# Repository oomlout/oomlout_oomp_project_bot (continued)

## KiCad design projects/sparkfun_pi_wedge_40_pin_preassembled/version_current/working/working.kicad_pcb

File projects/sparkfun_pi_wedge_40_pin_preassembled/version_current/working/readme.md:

# Pi_Wedge_40-Pin_PreAssembled by sparkfun  
This is a harvested standardized copy of a project from github.  
The original project can be found at:  
https://github.com/sparkfun/Pi_Wedge_40-Pin_PreAssembled  
Please consult that link for additional, details, files, and license information.  
Note: It was auto harvested and if the original repo had more than one board file or anything out of the ordinary the files here are likely not representative.

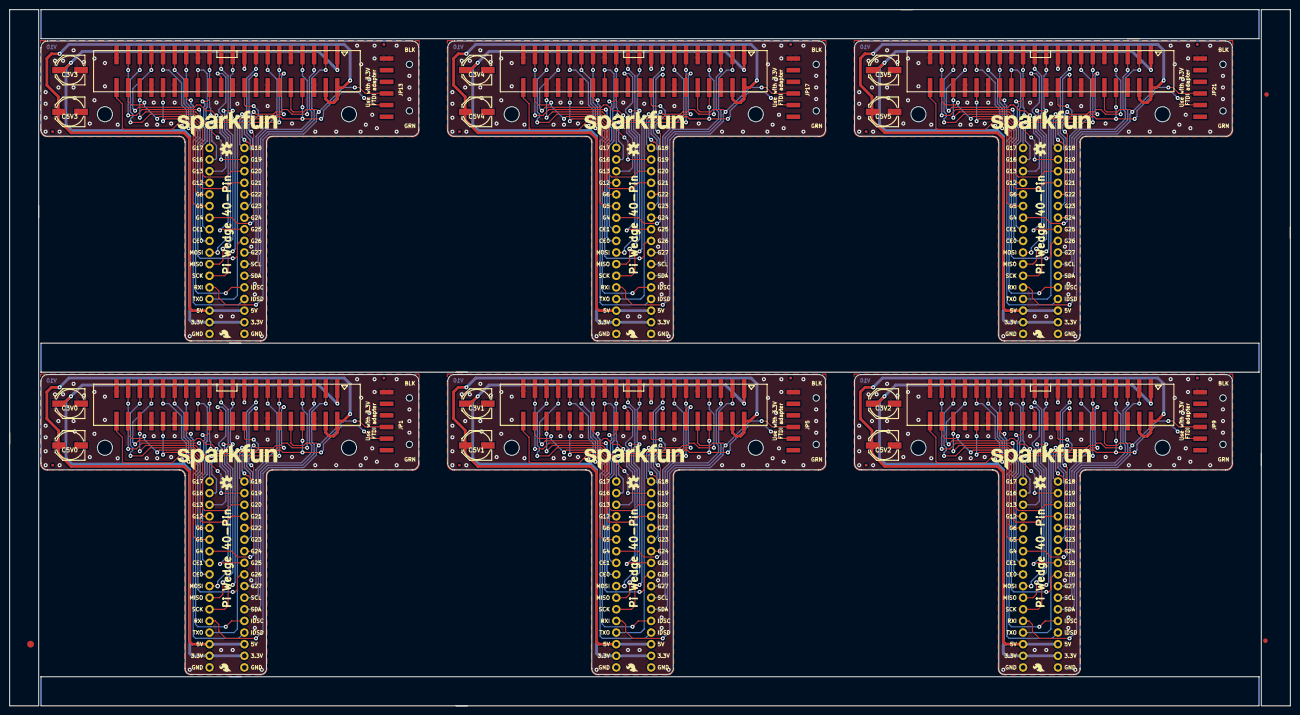
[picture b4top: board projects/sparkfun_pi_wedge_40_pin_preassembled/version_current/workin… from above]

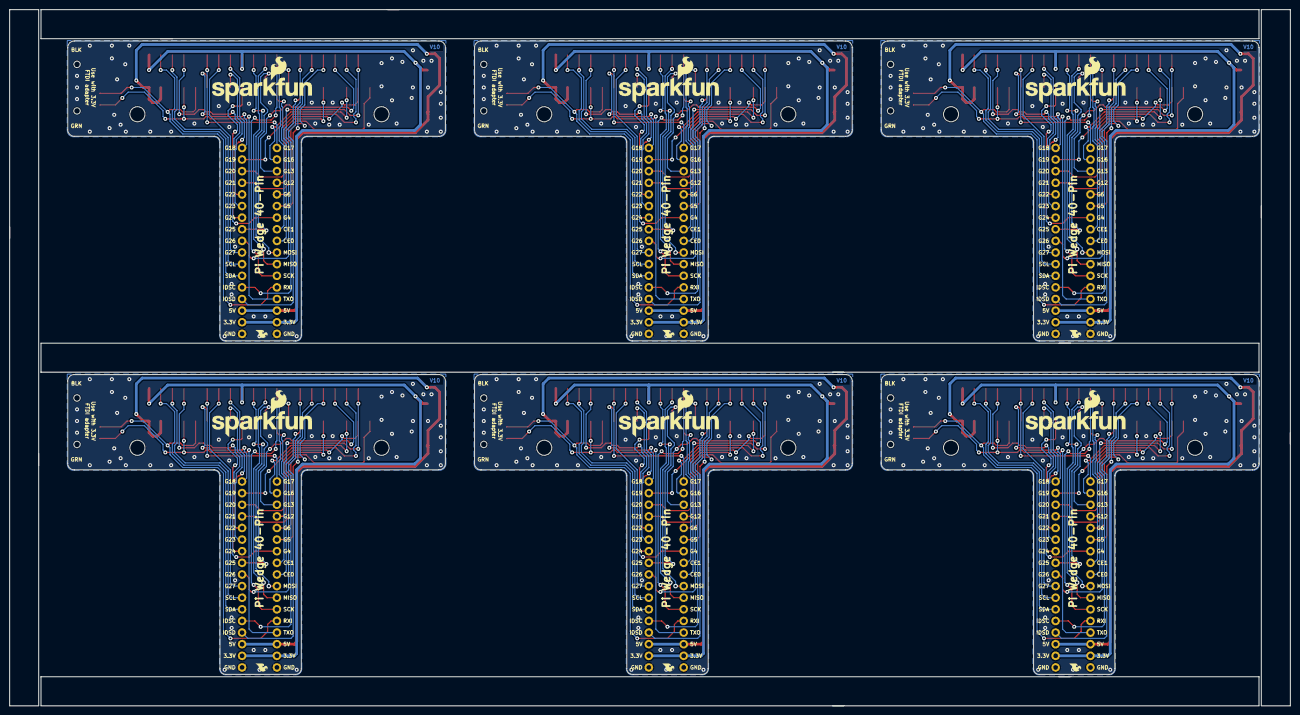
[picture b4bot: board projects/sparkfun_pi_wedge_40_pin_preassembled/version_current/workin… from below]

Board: 2 copper layers, 279.9 x 152.1 mm, 93 parts (24 on the bottom side), 186 nets.

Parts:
C3V0, C3V1, C3V2, C3V3, C3V4, C3V5, C5V0, C5V1, C5V2, C5V3, C5V4, C5V5: 10uf; PANASONIC_D
E$1: FIDUCIAL-1.5X3
E$5, E$6: FIDUCIAL-1X2
FID1, FID2, FID3, FID4, FID5, FID6, FID7, FID8, FID9, FID10, FID11, FID12: FIDUCIALUFIDUCIAL; MICRO-FIDUCIAL
JP1, JP5, JP9, JP13, JP17, JP21: FTDI Device; FTDI_DEVICE_RA_SMT
JP2, JP6, JP10, JP14, JP18, JP22: RASPBERRYPI-40-PIN-GPIO-SMT; 2X20-SHROUDED-SMT
JP3, JP4, JP7, JP8, JP11, JP12, JP15, JP16, JP19, JP20, JP23, JP24: 1x17; 1X17_NO_SILK_KIT
LOGO1, LOGO6, LOGO11, LOGO16, LOGO21, LOGO26: SFE_LOGO_NAME.2_INCH; SFE_LOGO_NAME_.2
LOGO2, LOGO7, LOGO12, LOGO17, LOGO22, LOGO27: SFE_LOGO_NAME_FLAME.2_INCH; SFE_LOGO_NAME_FLAME_.2
LOGO3, LOGO4, LOGO8, LOGO9, LOGO13, LOGO14, LOGO18, LOGO19, LOGO23, LOGO24, LOGO28, LOGO29: SFE_LOGO_FLAME.1_INCH; SFE_LOGO_FLAME_.1
LOGO5, LOGO10, LOGO15, LOGO20, LOGO25, LOGO30: OSHW-LOGOS; OSHW-LOGO-S
STANDOFF1, STANDOFF2, STANDOFF3, STANDOFF4, STANDOFF5, STANDOFF6, STANDOFF7, STANDOFF8, STANDOFF9, STANDOFF10, STANDOFF11, STANDOFF12: STAND-OFF

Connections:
3.3V: C3V0.+, JP2.1, JP2.17, JP3.2, JP4.2
3.3V1: C3V1.+, JP6.1, JP6.17, JP7.2, JP8.2
3.3V2: C3V2.+, JP10.1, JP10.17, JP11.2, JP12.2
3.3V3: C3V3.+, JP14.1, JP14.17, JP15.2, JP16.2
3.3V4: C3V4.+, JP18.1, JP18.17, JP19.2, JP20.2
3.3V5: C3V5.+, JP22.1, JP22.17, JP23.2, JP24.2
5V: C5V0.+, JP2.2, JP2.4, JP3.3, JP4.3
5V1: C5V1.+, JP6.2, JP6.4, JP7.3, JP8.3
5V2: C5V2.+, JP10.2, JP10.4, JP11.3, JP12.3
5V3: C5V3.+, JP14.2, JP14.4, JP15.3, JP16.3
5V4: C5V4.+, JP18.2, JP18.4, JP19.3, JP20.3
5V5: C5V5.+, JP22.2, JP22.4, JP23.3, JP24.3
CE0: JP2.24, JP3.9
CE1: JP2.26, JP3.10
CE2: JP6.24, JP7.9
CE3: JP6.26, JP7.10
CE4: JP10.24, JP11.9
CE5: JP10.26, JP11.10
CE6: JP14.24, JP15.9
CE7: JP14.26, JP15.10
CE8: JP18.24, JP19.9
CE9: JP18.26, JP19.10
CE10: JP22.24, JP23.9
CE11: JP22.26, JP23.10
GND: C3V0.-, C5V0.-, JP1.6, JP2.6, JP2.9, JP2.14, JP2.20, JP2.25, JP2.30, JP2.34, JP2.39, JP3.1, JP4.1
GND1: C3V1.-, C5V1.-, JP5.6, JP6.6, JP6.9, JP6.14, JP6.20, JP6.25, JP6.30, JP6.34, JP6.39, JP7.1, JP8.1
GND2: C3V2.-, C5V2.-, JP9.6, JP10.6, JP10.9, JP10.14, JP10.20, JP10.25, JP10.30, JP10.34, JP10.39, JP11.1, JP12.1
GND3: C3V3.-, C5V3.-, JP13.6, JP14.6, JP14.9, JP14.14, JP14.20, JP14.25, JP14.30, JP14.34, JP14.39, JP15.1, JP16.1
GND4: C3V4.-, C5V4.-, JP17.6, JP18.6, JP18.9, JP18.14, JP18.20, JP18.25, JP18.30, JP18.34, JP18.39, JP19.1, JP20.1
GND5: C3V5.-, C5V5.-, JP21.6, JP22.6, JP22.9, JP22.14, JP22.20, JP22.25, JP22.30, JP22.34, JP22.39, JP23.1, JP24.1
GP1: JP6.7, JP7.11
GP2: JP6.13, JP8.8
GP3: JP6.22, JP8.10
GP4: JP2.7, JP3.11
GP5: JP2.29, JP3.12
GP6: JP2.31, JP3.13
GP7: JP6.18, JP8.11
GP8: JP6.16, JP8.12
GP9: JP6.15, JP8.13
GP10: JP6.12, JP8.17
GP11: JP6.11, JP7.17
GP12: JP2.32, JP3.14
GP13: JP2.33, JP3.15
GP14: JP6.29, JP7.12
GP15: JP6.31, JP7.13
GP16: JP2.36, JP3.16
GP17: JP2.11, JP3.17
GP18: JP2.12, JP4.17
GP19: JP2.35, JP4.16
GP20: JP2.38, JP4.15
GP21: JP2.40, JP4.14
GP22: JP2.15, JP4.13
GP23: JP2.16, JP4.12
GP24: JP2.18, JP4.11
GP25: JP2.22, JP4.10
GP26: JP2.37, JP4.9
GP27: JP2.13, JP4.8
GP28: JP6.32, JP7.14
GP29: JP6.33, JP7.15
GP30: JP6.36, JP7.16
GP31: JP6.35, JP8.16
GP32: JP6.38, JP8.15
GP33: JP6.40, JP8.14
GP34: JP6.37, JP8.9
GP35: JP10.7, JP11.11
GP36: JP10.13, JP12.8
GP37: JP10.22, JP12.10
GP38: JP10.18, JP12.11
GP39: JP10.16, JP12.12
GP40: JP10.15, JP12.13
GP41: JP10.12, JP12.17
GP42: JP10.11, JP11.17
GP43: JP10.29, JP11.12
GP44: JP10.31, JP11.13
GP45: JP10.32, JP11.14
GP46: JP10.33, JP11.15
GP47: JP10.36, JP11.16
GP48: JP10.35, JP12.16
GP49: JP10.38, JP12.15
GP50: JP10.40, JP12.14
GP51: JP10.37, JP12.9
GP52: JP14.7, JP15.11
GP53: JP14.13, JP16.8
GP54: JP14.22, JP16.10
GP55: JP14.18, JP16.11
GP56: JP14.16, JP16.12
GP57: JP14.15, JP16.13
GP58: JP14.12, JP16.17
GP59: JP14.11, JP15.17
GP60: JP14.29, JP15.12
GP61: JP14.31, JP15.13
GP62: JP14.32, JP15.14
GP63: JP14.33, JP15.15
GP64: JP14.36, JP15.16
GP65: JP14.35, JP16.16
GP66: JP14.38, JP16.15
GP67: JP14.40, JP16.14
GP68: JP14.37, JP16.9
GP69: JP18.7, JP19.11
GP70: JP18.13, JP20.8
GP71: JP18.22, JP20.10
GP72: JP18.18, JP20.11
GP73: JP18.16, JP20.12
GP74: JP18.15, JP20.13
GP75: JP18.12, JP20.17
GP76: JP18.11, JP19.17
GP77: JP18.29, JP19.12
GP78: JP18.31, JP19.13
GP79: JP18.32, JP19.14
GP80: JP18.33, JP19.15
GP81: JP18.36, JP19.16
GP82: JP18.35, JP20.16
GP83: JP18.38, JP20.15
GP84: JP18.40, JP20.14
GP85: JP18.37, JP20.9
GP86: JP22.7, JP23.11
GP87: JP22.13, JP24.8
GP88: JP22.22, JP24.10
GP89: JP22.18, JP24.11
GP90: JP22.16, JP24.12
GP91: JP22.15, JP24.13
GP92: JP22.12, JP24.17
GP93: JP22.11, JP23.17
GP94: JP22.29, JP23.12
GP95: JP22.31, JP23.13
GP96: JP22.32, JP23.14
GP97: JP22.33, JP23.15
GP98: JP22.36, JP23.16
GP99: JP22.35, JP24.16
GP100: JP22.38, JP24.15
GP101: JP22.40, JP24.14
GP102: JP22.37, JP24.9
ID_SC: JP2.28, JP4.5
ID_SC1: JP6.28, JP8.5
ID_SC2: JP10.28, JP12.5
ID_SC3: JP14.28, JP16.5
ID_SC4: JP18.28, JP20.5
ID_SC5: JP22.28, JP24.5
ID_SD: JP2.27, JP4.4
ID_SD1: JP6.27, JP8.4
ID_SD2: JP10.27, JP12.4
ID_SD3: JP14.27, JP16.4
ID_SD4: JP18.27, JP20.4
ID_SD5: JP22.27, JP24.4
MISO: JP2.21, JP3.7
MISO1: JP6.21, JP7.7
MISO2: JP10.21, JP11.7
MISO3: JP14.21, JP15.7
MISO4: JP18.21, JP19.7
MISO5: JP22.21, JP23.7
MOSI: JP2.19, JP3.8
MOSI1: JP6.19, JP7.8
MOSI2: JP10.19, JP11.8
MOSI3: JP14.19, JP15.8
MOSI4: JP18.19, JP19.8
MOSI5: JP22.19, JP23.8
RXI: JP1.3, JP2.10, JP3.5
RXI1: JP5.3, JP6.10, JP7.5
RXI2: JP9.3, JP10.10, JP11.5
RXI3: JP13.3, JP14.10, JP15.5
RXI4: JP17.3, JP18.10, JP19.5
RXI5: JP21.3, JP22.10, JP23.5
SCL: JP2.5, JP4.7
SCL1: JP6.5, JP8.7
SCL2: JP10.5, JP12.7
SCL3: JP14.5, JP16.7
SCL4: JP18.5, JP20.7
SCL5: JP22.5, JP24.7
SCLK: JP2.23, JP3.6
SCLK1: JP6.23, JP7.6
SCLK2: JP10.23, JP11.6
SCLK3: JP14.23, JP15.6
SCLK4: JP18.23, JP19.6
SCLK5: JP22.23, JP23.6
SDA: JP2.3, JP4.6
SDA1: JP6.3, JP8.6
SDA2: JP10.3, JP12.6
SDA3: JP14.3, JP16.6
SDA4: JP18.3, JP20.6
SDA5: JP22.3, JP24.6
TXO: JP1.2, JP2.8, JP3.4
TXO1: JP5.2, JP6.8, JP7.4
TXO2: JP9.2, JP10.8, JP11.4
TXO3: JP13.2, JP14.8, JP15.4
TXO4: JP17.2, JP18.8, JP19.4
TXO5: JP21.2, JP22.8, JP23.4

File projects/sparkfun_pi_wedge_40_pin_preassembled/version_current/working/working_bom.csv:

Row,Description,Part,References,Value,Footprint,Quantity Per PCB,Status,Datasheet
1,,47UF-50V-20%(ELECT),C3V0 C5V0,47uf,PANASONIC_D,2, ,
2,,FRAME-LETTER,FRAME2,FRAME-LETTER,CREATIVE_COMMONS,1, ,
3,,M17KIT,JP3 JP4,1x17,1X17_NO_SILK_KIT,2, ,
4,,FTDI_DEVICERA_SMT,JP1,FTDI_DEVICERA_SMT,FTDI_DEVICE_RA_SMT,1, ,
5,,RASPBERRYPI-40-PIN-GPIO-SMT,JP2,RASPBERRYPI-40-PIN-GPIO-SMT,2X20-SHROUDED-SMT,1, ,
6,,OSHW-LOGOS,LOGO5,OSHW-LOGOS,OSHW-LOGO-S,1, ,
7,,SFE_LOGO_FLAME.1_INCH,LOGO3 LOGO4,SFE_LOGO_FLAME.1_INCH,SFE_LOGO_FLAME_.1,2, ,
8,,SFE_LOGO_NAME.2_INCH,LOGO1,SFE_LOGO_NAME.2_INCH,SFE_LOGO_NAME_.2,1, ,
9,,SFE_LOGO_NAME_FLAME.2_INCH,LOGO2,SFE_LOGO_NAME_FLAME.2_INCH,SFE_LOGO_NAME_FLAME_.2,1, ,
10,,STAND-OFF,STANDOFF1 STANDOFF2,STAND-OFF,STAND-OFF,2, ,
11,,BREADBOARD_PATTERN,U$2,BREADBOARD_PATTERN,BREADBOARD_SPACING,1, ,





Project info:
Schematic:,working
Variant:,default
Revision:,
Date:,2023-08-06_12-56-12
KiCad Version:,7.0.6-7.0.6~ubuntu22.04.1
Statistics:
Component Groups:,11
Component Count:,15 (0 SMD/ 0 THT)
Fitted Components:,15 (0 SMD/ 0 THT)
Number of PCBs:,1
Total Components:,15

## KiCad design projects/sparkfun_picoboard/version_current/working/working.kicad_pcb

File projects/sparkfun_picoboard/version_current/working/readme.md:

# OOMP Project  
## PicoBoard  by sparkfun  
  
oomp key: oomp_projects_flat_sparkfun_picoboard  
(snippet of original readme)  
  
Picoboard  
=========  
  
[   
*PicoBoard (WIG-10311)*](https://www.sparkfun.com/products/10311)  
  
The PicoBoard allows you to interface hardware sensors with the Scratch programming language.  

Repository Contents  
-------------------  
* **/hardware** - All Eagle design files (.brd, .sch, .STL)  
* **/firmware** - PicoBoard source code for an ATmega328.  
  
License Information  
-------------------  
The contents released under [Creative Commons Share-alike 3.0](http://creativecommons.org/licenses/by-sa/3.0/).    
  full source readme at [readme_src.md](readme_src.md)  
  
source repo at: [https://github.com/sparkfun/PicoBoard](https://github.com/sparkfun/PicoBoard)  
## Board  

## Schematic  

[schematic pdf](working_schematic.pdf)  
## Images

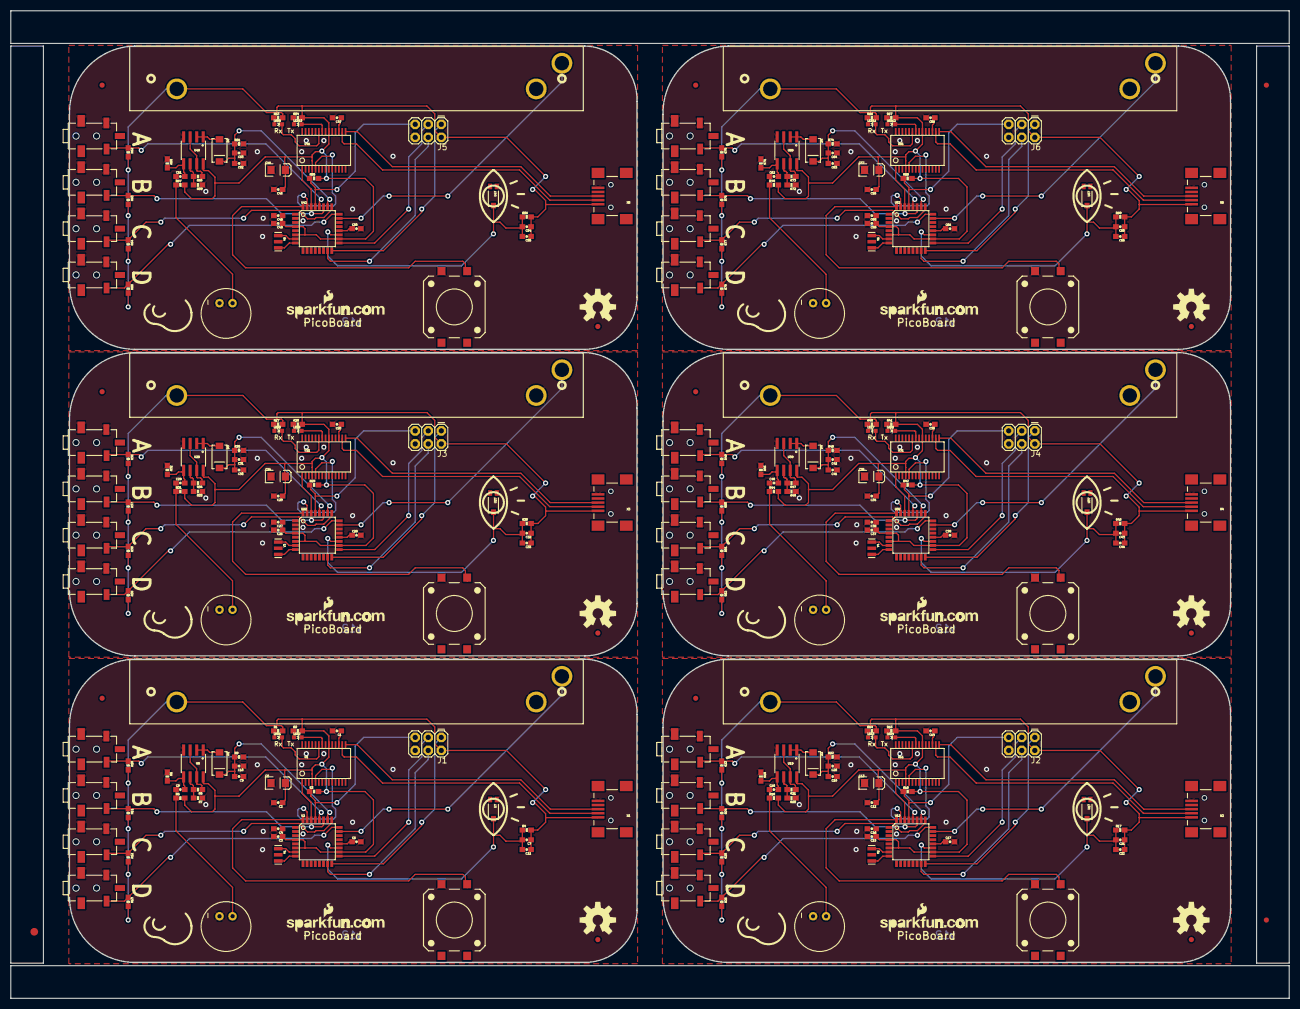
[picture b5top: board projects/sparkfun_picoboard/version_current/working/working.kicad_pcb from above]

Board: 2 copper layers, 248.9 x 192.3 mm, 273 parts (0 on the bottom side), 186 nets.

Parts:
C1, C2, C3, C4, C6, C8, C9, C10, C11, C12, C14, C15, C16, C17, C18, C19, C20, C22, C23, C25, C26, C27, C28, C29, C30, C31, C33, C34, C36, C37, C38, C39, C40, C41, C42, C44, C45, C47, C48, C49, C50, C51, C52, C53, C55, C56, C58, C59, C60, C61, C62, C63, C64, C66: 0.1uF; 0603-CAP
C5, C13, C24, C35, C46, C57: 10uF; EIA3216
C7, C21, C32, C43, C54, C65: 0.22uF; 0603-CAP
D1, D2, D3, D4, D5, D6: MBRA140; SMA-DIODE
E$1: FIDUCIAL-1.5X3
E$2, E$4: FIDUCIAL-1X2
FID1, FID2, FID3, FID4, FID5, FID6, FID7, FID8, FID9, FID10, FID11, FID12: FIDUCIAL1X2; FIDUCIAL-1X2
J1, J2, J3, J4, J5, J6: AVR Prog.; 2X3
JP1, JP2, JP3, JP4, JP5, JP6: LOGO-SFENEW; SFE-NEW-WEBLOGO
LED1, LED3, LED5, LED7, LED9, LED11: Red; LED-0603
LED2, LED4, LED6, LED8, LED10, LED12: Green; LED-0603
LOGO1, LOGO2, LOGO3, LOGO4, LOGO5, LOGO6: OSHW-LOGOL; OSHW-LOGO-L
R1, R2, R14, R15, R27, R28, R40, R41, R53, R54, R66, R67: 1K; 0603-RES
R3, R5, R6, R10, R11, R12, R13, R16, R18, R19, R23, R24, R25, R26, R29, R31, R32, R36, R37, R38, R39, R42, R44, R45, R49, R50, R51, R52, R55, R57, R58, R62, R63, R64, R65, R68, R70, R71, R75, R76, R77, R78: 10k; 0603-RES
R4, R8, R9, R17, R21, R22, R30, R34, R35, R43, R47, R48, R56, R60, R61, R69, R73, R74: 100k; 0603-RES
R7, R20, R33, R46, R59, R72: 2.2k; 0603-RES
S1, S2, S3, S4, S5, S6: 12mm Button; TACTILE-SMD-12MM
U1, U11, U21, U31, U41, U51: FT232RLSSOP; SSOP28DB
U2, U12, U22, U32, U42, U52: ATMEGA328; TQFP32-08
U3, U4, U5, U6, U13, U14, U15, U16, U23, U24, U25, U26, U33, U34, U35, U36, U43, U44, U45, U46, U53, U54, U55, U56: 2.5mm; STEREOJACK2.5MM
U7, U17, U27, U37, U47, U57: TEMT6000; TEMT6000-SEN
U8, U19, U29, U39, U49, U59: LMV358; SO08
U9, U18, U28, U38, U48, U58: MIC9.7MM; MIC-9.7MM
U10, U20, U30, U40, U50, U60: SLIDER
X1, X2, X3, X4, X5, X6: USBSMD; USB-MINIB
Y1, Y2, Y3, Y4, Y5, Y6: 16MHz; RESONATOR-SMD

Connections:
3.3V: C1.1, U1.17
3.3V1: C14.1, U11.17
3.3V2: C25.1, U21.17
3.3V3: C36.1, U31.17
3.3V4: C47.1, U41.17
3.3V5: C58.1, U51.17
5V: C2.1, C3.1, C4.1, C5.A, C7.1, C11.1, J1.2, R1.2, R2.2, R3.2, R4.2, R5.2, R10.2, R11.2, R12.2, R13.2, U1.4, U1.20, U2.4, U2.6, U2.18, U8.8, U10.3, X1.VBUS
5V1: C12.1, C13.A, C15.1, C16.1, C21.1, C22.1, J2.2, R14.2, R15.2, R16.2, R17.2, R18.2, R23.2, R24.2, R25.2, R26.2, U11.4, U11.20, U12.4, U12.6, U12.18, U19.8, U20.3, X2.VBUS
5V2: C23.1, C24.A, C26.1, C27.1, C32.1, C33.1, J3.2, R27.2, R28.2, R29.2, R30.2, R31.2, R36.2, R37.2, R38.2, R39.2, U21.4, U21.20, U22.4, U22.6, U22.18, U29.8, U30.3, X3.VBUS
5V3: C34.1, C35.A, C37.1, C38.1, C43.1, C44.1, J4.2, R40.2, R41.2, R42.2, R43.2, R44.2, R49.2, R50.2, R51.2, R52.2, U31.4, U31.20, U32.4, U32.6, U32.18, U39.8, U40.3, X4.VBUS
5V4: C45.1, C46.A, C48.1, C49.1, C54.1, C55.1, J5.2, R53.2, R54.2, R55.2, R56.2, R57.2, R62.2, R63.2, R64.2, R65.2, U41.4, U41.20, U42.4, U42.6, U42.18, U49.8, U50.3, X5.VBUS
5V5: C56.1, C57.A, C59.1, C60.1, C65.1, C66.1, J6.2, R66.2, R67.2, R68.2, R69.2, R70.2, R75.2, R76.2, R77.2, R78.2, U51.4, U51.20, U52.4, U52.6, U52.18, U59.8, U60.3, X6.VBUS
GND: C1.2, C2.2, C3.2, C4.2, C5.C, C6.2, C9.1, C10.1, J1.6, R6.1, R7.1, R9.2, S2.3, U1.7, U1.18, U1.21, U1.25, U1.26, U2.3, U2.5, U2.21, U3.1, U3.5, U4.1, U4.5, U5.1, U5.5, U6.1, U6.5, U7.EMITTER, U8.4, U9.2, U10.1, X1.GND, Y1.2
GND1: C12.2, C13.C, C14.2, C15.2, C16.2, C17.2, C19.1, C20.1, J2.6, R19.1, R20.1, R22.2, S1.3, U11.7, U11.18, U11.21, U11.25, U11.26, U12.3, U12.5, U12.21, U13.1, U13.5, U14.1, U14.5, U15.1, U15.5, U16.1, U16.5, U17.EMITTER, U18.2, U19.4, U20.1, X2.GND, Y2.2
GND2: C23.2, C24.C, C25.2, C26.2, C27.2, C28.2, C30.1, C31.1, J3.6, R32.1, R33.1, R35.2, S3.3, U21.7, U21.18, U21.21, U21.25, U21.26, U22.3, U22.5, U22.21, U23.1, U23.5, U24.1, U24.5, U25.1, U25.5, U26.1, U26.5, U27.EMITTER, U28.2, U29.4, U30.1, X3.GND, Y3.2
GND3: C34.2, C35.C, C36.2, C37.2, C38.2, C39.2, C41.1, C42.1, J4.6, R45.1, R46.1, R48.2, S4.3, U31.7, U31.18, U31.21, U31.25, U31.26, U32.3, U32.5, U32.21, U33.1, U33.5, U34.1, U34.5, U35.1, U35.5, U36.1, U36.5, U37.EMITTER, U38.2, U39.4, U40.1, X4.GND, Y4.2
GND4: C45.2, C46.C, C47.2, C48.2, C49.2, C50.2, C52.1, C53.1, J5.6, R58.1, R59.1, R61.2, S5.3, U41.7, U41.18, U41.21, U41.25, U41.26, U42.3, U42.5, U42.21, U43.1, U43.5, U44.1, U44.5, U45.1, U45.5, U46.1, U46.5, U47.EMITTER, U48.2, U49.4, U50.1, X5.GND, Y5.2
GND5: C56.2, C57.C, C58.2, C59.2, C60.2, C61.2, C63.1, C64.1, J6.6, R71.1, R72.1, R74.2, S6.3, U51.7, U51.18, U51.21, U51.25, U51.26, U52.3, U52.5, U52.21, U53.1, U53.5, U54.1, U54.5, U55.1, U55.5, U56.1, U56.5, U57.EMITTER, U58.2, U59.4, U60.1, X6.GND, Y6.2
LIGHT: C7.2, C11.2, R4.1, U2.19, U7.COLLECTOR
LIGHT1: C21.2, C22.2, R17.1, U12.19, U17.COLLECTOR
LIGHT2: C32.2, C33.2, R30.1, U22.19, U27.COLLECTOR
LIGHT3: C43.2, C44.2, R43.1, U32.19, U37.COLLECTOR
LIGHT4: C54.2, C55.2, R56.1, U42.19, U47.COLLECTOR
LIGHT5: C65.2, C66.2, R69.1, U52.19, U57.COLLECTOR
MISO: J1.1, U2.16
MISO1: J2.1, U12.16
MISO2: J3.1, U22.16
MISO3: J4.1, U32.16
MISO4: J5.1, U42.16
MISO5: J6.1, U52.16
MOSI: J1.4, U2.15
MOSI1: J2.4, U12.15
MOSI2: J3.4, U22.15
MOSI3: J4.4, U32.15
MOSI4: J5.4, U42.15
MOSI5: J6.4, U52.15
unnamed: LED1.A, R1.1
unnamed: LED2.A, R2.1
unnamed: R7.2, R8.2, U8.6
unnamed: LED3.A, R14.1
unnamed: U2.7, Y1.1
unnamed: U2.8, Y1.3
unnamed: C6.1, U2.20
unnamed: S2.1, U2.32
unnamed: C8.1, R5.1, U9.1
unnamed: U2.23, U10.2A
unnamed: C8.2, R6.2, U8.5
unnamed: LED4.A, R15.1
unnamed: D1.A, U8.1, U8.2
unnamed: U12.7, Y2.1
unnamed: U12.8, Y2.3
unnamed: R8.1, U8.3, U8.7
unnamed: C17.1, U12.20
unnamed: S1.1, U12.32
unnamed: C18.1, R18.1, U18.1
unnamed: C18.2, R19.2, U19.5
unnamed: R20.2, R21.2, U19.6
unnamed: D2.A, U19.1, U19.2
unnamed: R21.1, U19.3, U19.7
unnamed: U12.23, U20.2A
unnamed: LED5.A, R27.1
unnamed: LED6.A, R28.1
unnamed: U22.7, Y3.1
unnamed: U22.8, Y3.3
unnamed: C28.1, U22.20
unnamed: S3.1, U22.32
unnamed: C29.1, R31.1, U28.1
unnamed: C29.2, R32.2, U29.5
unnamed: R33.2, R34.2, U29.6
unnamed: D3.A, U29.1, U29.2
unnamed: R34.1, U29.3, U29.7
unnamed: U22.23, U30.2A
unnamed: LED7.A, R40.1
unnamed: LED8.A, R41.1
unnamed: U32.7, Y4.1
unnamed: U32.8, Y4.3
unnamed: C39.1, U32.20
unnamed: S4.1, U32.32
unnamed: C40.1, R44.1, U38.1
unnamed: C40.2, R45.2, U39.5
unnamed: R46.2, R47.2, U39.6
unnamed: D4.A, U39.1, U39.2
unnamed: R47.1, U39.3, U39.7
unnamed: U32.23, U40.2A
unnamed: LED9.A, R53.1
unnamed: LED10.A, R54.1
unnamed: U42.7, Y5.1
unnamed: U42.8, Y5.3
unnamed: C50.1, U42.20
unnamed: S5.1, U42.32
unnamed: C51.1, R57.1, U48.1
unnamed: C51.2, R58.2, U49.5
unnamed: R59.2, R60.2, U49.6
unnamed: D5.A, U49.1, U49.2
unnamed: R60.1, U49.3, U49.7
unnamed: U42.23, U50.2A
unnamed: LED11.A, R66.1
unnamed: LED12.A, R67.1
unnamed: U52.7, Y6.1
unnamed: U52.8, Y6.3
unnamed: C61.1, U52.20
unnamed: S6.1, U52.32
unnamed: C62.1, R70.1, U58.1
unnamed: C62.2, R71.2, U59.5
unnamed: R72.2, R73.2, U59.6
unnamed: D6.A, U59.1, U59.2
unnamed: R73.1, U59.3, U59.7
unnamed: U52.23, U60.2A
RA: R10.1, U2.28, U3.4
RA1: R23.1, U12.28, U13.4
RA2: R36.1, U22.28, U23.4
RA3: R49.1, U32.28, U33.4
RA4: R62.1, U42.28, U43.4
RA5: R75.1, U52.28, U53.4
RB: R11.1, U2.27, U4.4
RB1: R24.1, U12.27, U14.4
RB2: R37.1, U22.27, U24.4
RB3: R50.1, U32.27, U34.4
RB4: R63.1, U42.27, U44.4
RB5: R76.1, U52.27, U54.4
RC: R12.1, U2.25, U5.4
RC1: R25.1, U12.25, U15.4
RC2: R38.1, U22.25, U25.4
RC3: R51.1, U32.25, U35.4
RC4: R64.1, U42.25, U45.4
RC5: R77.1, U52.25, U55.4
RD: R13.1, U2.24, U6.4
RD1: R26.1, U12.24, U16.4
RD2: R39.1, U22.24, U26.4
RD3: R52.1, U32.24, U36.4
RD4: R65.1, U42.24, U46.4
RD5: R78.1, U52.24, U56.4
RES: J1.5, R3.1, U2.29
RES1: J2.5, R16.1, U12.29
RES2: J3.5, R29.1, U22.29
RES3: J4.5, R42.1, U32.29
RES4: J5.5, R55.1, U42.29
RES5: J6.5, R68.1, U52.29
RXI: U1.1, U2.30
RXI1: U11.1, U12.30
RXI2: U21.1, U22.30
RXI3: U31.1, U32.30
RXI4: U41.1, U42.30
RXI5: U51.1, U52.30
RXLED: LED2.C, U1.22
RXLED1: LED4.C, U11.22
RXLED2: LED6.C, U21.22
RXLED3: LED8.C, U31.22
RXLED4: LED10.C, U41.22
RXLED5: LED12.C, U51.22
SCK: J1.3, U2.17
SCK1: J2.3, U12.17
SCK2: J3.3, U22.17
SCK3: J4.3, U32.17
SCK4: J5.3, U42.17
SCK5: J6.3, U52.17
SOUND: C9.2, C10.2, D1.C, R9.1, U2.26
SOUND1: C19.2, C20.2, D2.C, R22.1, U12.26
SOUND2: C30.2, C31.2, D3.C, R35.1, U22.26
SOUND3: C41.2, C42.2, D4.C, R48.1, U32.26
SOUND4: C52.2, C53.2, D5.C, R61.1, U42.26
SOUND5: C63.2, C64.2, D6.C, R74.1, U52.26
TXLED: LED1.C, U1.23
TXLED1: LED3.C, U11.23
TXLED2: LED5.C, U21.23
TXLED3: LED7.C, U31.23
TXLED4: LED9.C, U41.23
TXLED5: LED11.C, U51.23
TXO: U1.5, U2.31
TXO1: U11.5, U12.31
TXO2: U21.5, U22.31
TXO3: U31.5, U32.31
TXO4: U41.5, U42.31
TXO5: U51.5, U52.31
USB_D+: U1.15, X1.D+
USB_D+1: U11.15, X2.D+
USB_D+2: U21.15, X3.D+
USB_D+3: U31.15, X4.D+
USB_D+4: U41.15, X5.D+
USB_D+5: U51.15, X6.D+
USB_D-: U1.16, X1.D-
USB_D-1: U11.16, X2.D-
USB_D-2: U21.16, X3.D-
USB_D-3: U31.16, X4.D-
USB_D-4: U41.16, X5.D-
USB_D-5: U51.16, X6.D-

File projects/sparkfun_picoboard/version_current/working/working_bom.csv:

Row,Description,Part,References,Value,Footprint,Quantity Per PCB,Status,Datasheet
1,,CAP0603-CAP,C1 C2 C3 C4 C6 C8 C9 C10 C11,0.1uF,0603-CAP,9, ,
2,,CAP0603-CAP,C7,0.22uF,0603-CAP,1, ,
3,,CAP_POL1206,C5,10uF,EIA3216,1, ,
4,,DIODESMA,D1,MBRA140,SMA-DIODE,1, ,
5,,FRAME-LETTER,FRAME1,FRAME-LETTER,CREATIVE_COMMONS,1, ,
6,,AVR_SPI_PRG_6PTH,J1,AVR_SPI_PRG_6PTH,2X3,1, ,
7,,LOGO-SFENEW,JP1,LOGO-SFENEW,SFE-NEW-WEBLOGO,1, ,
8,,LED0603,LED2,Green,LED-0603,1, ,
9,,LED0603,LED1,Red,LED-0603,1, ,
10,,OSHW-LOGOL,LOGO1,OSHW-LOGOL,OSHW-LOGO-L,1, ,
11,,RESISTOR0603-RES,R1 R2,1K,0603-RES,2, ,
12,,RESISTOR0603-RES,R7,2.2k,0603-RES,1, ,
13,,RESISTOR0603-RES,R3 R5 R6 R10 R11 R12 R13,10k,0603-RES,7, ,
14,,RESISTOR0603-RES,R4 R8 R9,100k,0603-RES,3, ,
15,,SWITCH-MOMENTARY-2SMD-12MM,S2,SWITCH-MOMENTARY-2SMD-12MM,TACTILE-SMD-12MM,1, ,
16,,AUDIO-JACK1{colon}1,U3 U4 U5 U6,2.5mm,STEREOJACK2.5MM,4, ,
17,,ATMEGA168,U2,ATMEGA168,TQFP32-08,1, ,
18,,FT232RLSSOP,U1,FT232RLSSOP,SSOP28DB,1, ,
19,,LMV358,U8,LMV358,SO08,1, ,
20,,MIC9.7MM,U9,MIC9.7MM,MIC-9.7MM,1, ,
21,,SLIDER60MM,U10,SLIDER60MM,SLIDER,1, ,
22,,TEMT6000,U7,TEMT6000,TEMT6000-SEN,1, ,
23,,USBSMD,X1,USBSMD,USB-MINIB,1, ,
24,,RESONATORSMD,Y1,RESONATORSMD,RESONATOR-SMD,1, ,





Project info:
Schematic:,working
Variant:,default
Revision:,
Date:,2023-08-06_12-56-12
KiCad Version:,7.0.6-7.0.6~ubuntu22.04.1
Statistics:
Component Groups:,24
Component Count:,44 (0 SMD/ 0 THT)
Fitted Components:,44 (0 SMD/ 0 THT)
Number of PCBs:,1
Total Components:,44

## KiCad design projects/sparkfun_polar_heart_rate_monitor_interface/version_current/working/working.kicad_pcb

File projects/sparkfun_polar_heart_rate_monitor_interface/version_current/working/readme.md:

# OOMP Project  
## Polar_Heart_Rate_Monitor_Interface  by sparkfun  
  
oomp key: oomp_projects_flat_sparkfun_polar_heart_rate_monitor_interface  
(snippet of original readme)  
  
SparkFun Polar Heart Rate Monitor Interface  
========================================  

[*SparkFun Polar Heart Rate Monitor Interface (SEN-08661)*](https://www.sparkfun.com/products/8661)  
  
The Heart Rate Monitor Interface (HRMI) is an intelligent peripheral device that converts the ECG signal from the Polar Heart Rate Monitor (HRM)   
into easy-to-use heart rate data.  
  
Repository Contents  
-------------------  
* **/Hardware** - All Eagle design files (.brd, .sch)  

License Information  
-------------------  
The hardware is released under [Creative Commons ShareAlike 4.0 International](https://creativecommons.org/licenses/by-sa/4.0/).  
  
This product is a collaboration with Dan Julio. A portion of each sales goes back to them for product support and continued development.  
  
Distributed as-is; no warranty is given.  
  
  full source readme at [readme_src.md](readme_src.md)  
  
source repo at: [https://github.com/sparkfun/Polar_Heart_Rate_Monitor_Interface](https://github.com/sparkfun/Polar_Heart_Rate_Monitor_Interface)  
## Board  

## Schematic  

[schematic pdf](working_schematic.pdf)  
## Images

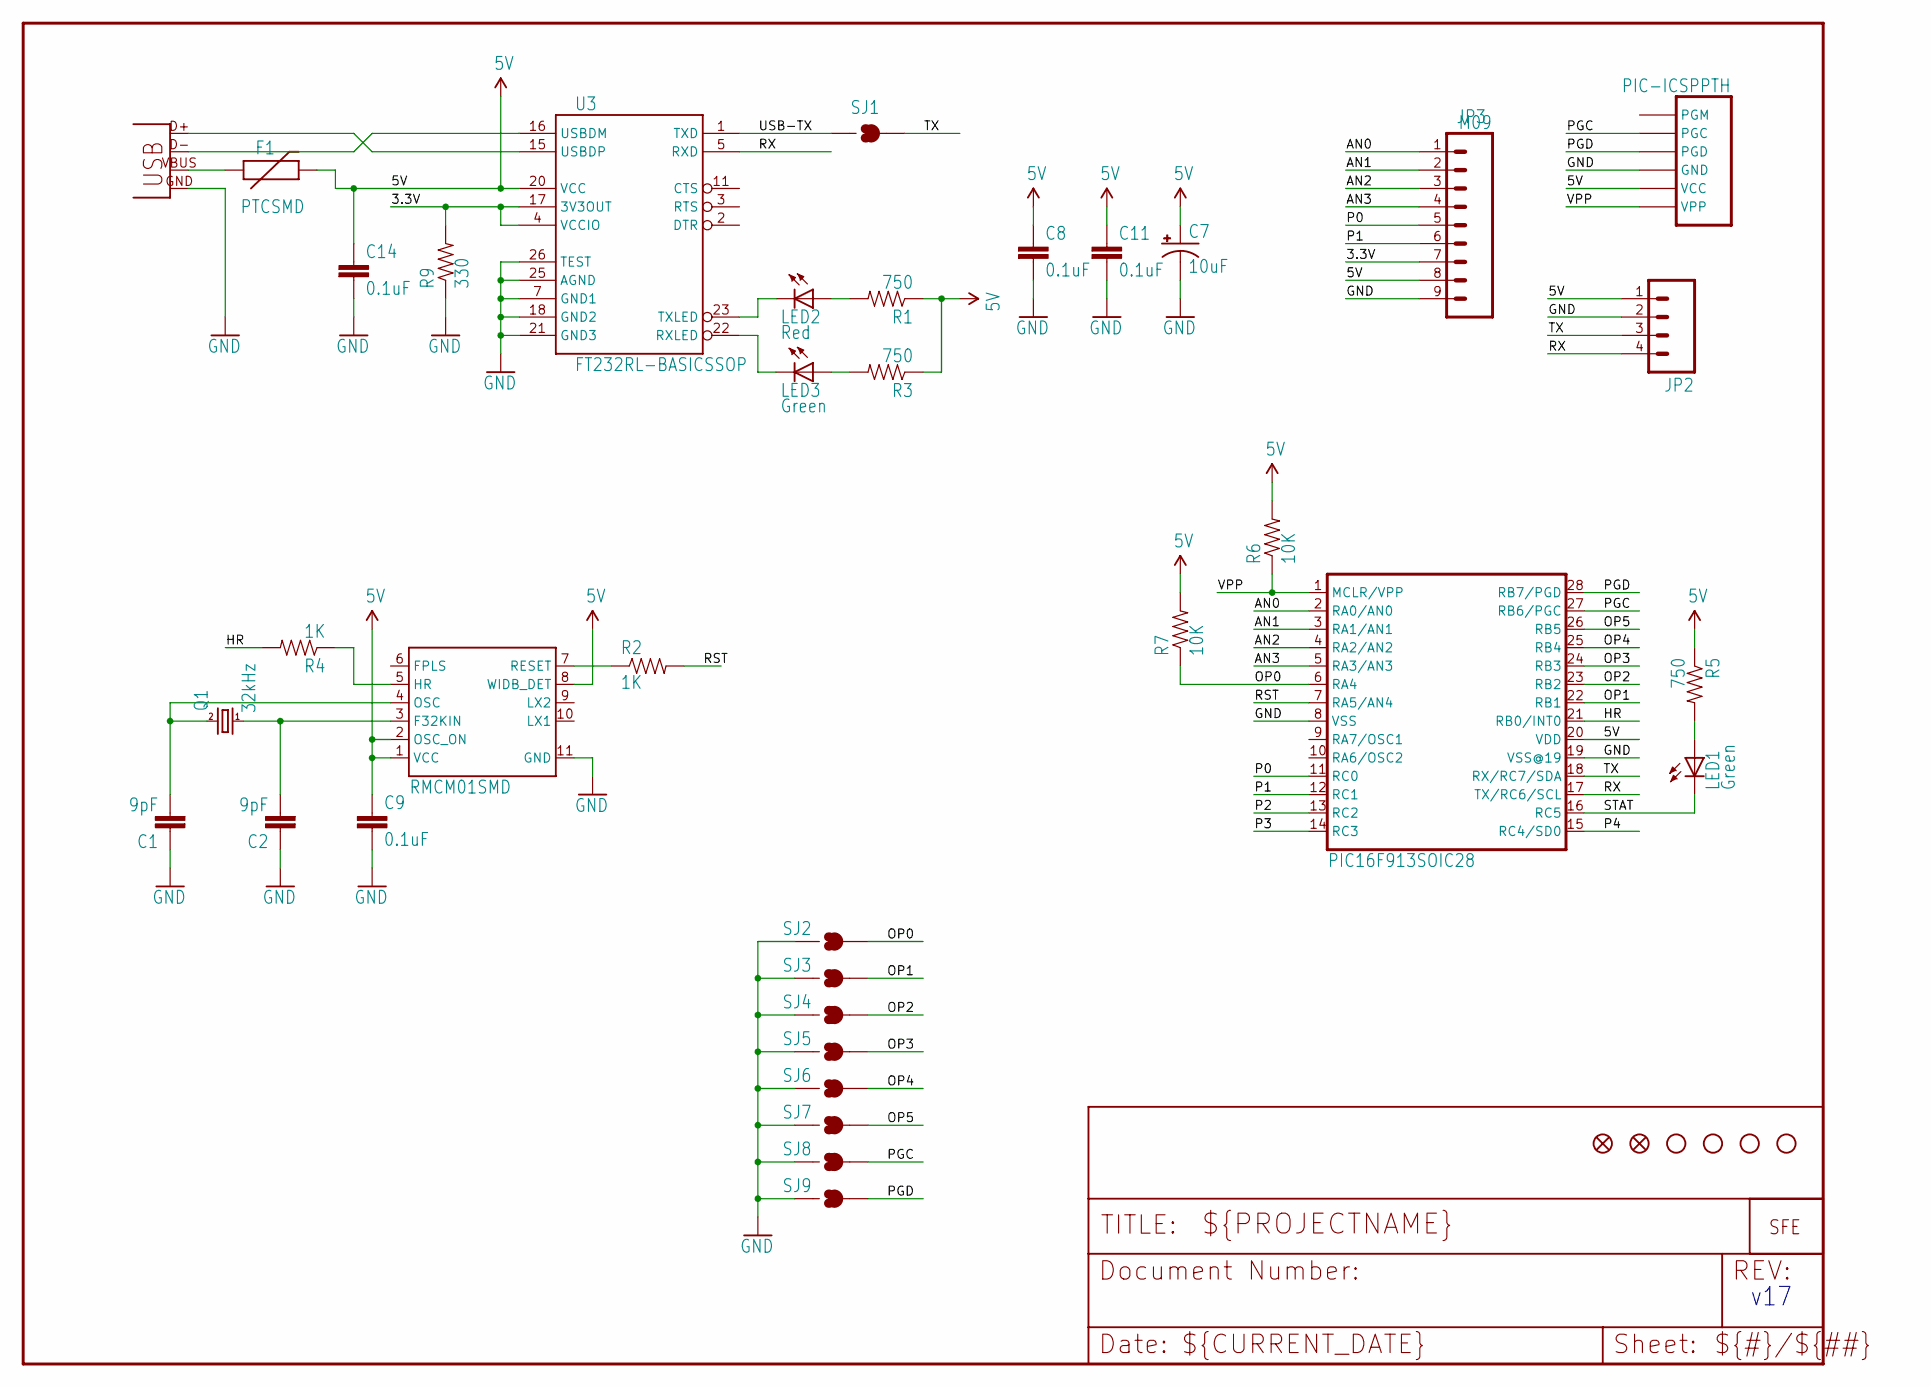
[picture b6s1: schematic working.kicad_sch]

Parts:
C1, C2: 9pF; 0402-CAP
C7: 10uF; EIA3216
C8, C9, C11, C14: 0.1uF; 0402-CAP
F1: PTCSMD; PTC-1206
JP2: M04PTH; 1X04
JP3: M09; 1X09
LED1, LED3: Green; LED-0603
LED2: Red; LED-0603
Q1: 32kHz; CRYSTAL-32KHZ-SMD_EPSON_MC146
R1, R3, R5: 750; 0402-RES
R2, R4: 1K; 0402-RES
R6, R7: 10K; 0402-RES
R9: 330; 0402-RES
SJ1: SOLDERJUMPERNC2; SJ_2S-NOTRACE
SJ2, SJ3, SJ4, SJ5, SJ6, SJ7, SJ8, SJ9: SOLDERJUMPERNO; SJ_2S-NO
U1: RMCM01SMD; RMCM01
U2: PIC16F913SOIC28; SO-28W
U3: FT232RL-BASICSSOP; SSOP28DB
U10: PIC-ICSPPTH; MOLEX-1X6
U$1: LOGO-SFENEW; SFE-NEW-WEBLOGO
U$4, U$8: FIDUCIAL1X2; FIDUCIAL-1X2
U$13, U$15, U$16, U$17: STAND-OFF
X1: USBSMD; USB-MINIB

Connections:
AN0: JP3.1, U2.2 (RA0/AN0)
AN1: JP3.2, U2.3 (RA1/AN1)
AN2: JP3.3, U2.4 (RA2/AN2)
AN3: JP3.4, U2.5 (RA3/AN3)
GND: C1.1, C2.1, C7.C (-), C8.2, C9.2, C11.2, C14.2, JP2.2, JP3.9, R9.1, SJ2.1, SJ3.1, SJ4.1, SJ5.1, SJ6.1, SJ7.1, SJ8.1, SJ9.1, U1.11 (GND), U2.8 (VSS), U2.19 (VSS@19), U3.7 (GND1), U3.18 (GND2), U3.21 (GND3), U3.25 (AGND), U3.26 (TEST), U10.4 (GND), X1.GND
HR: R4.2, U2.21 (RB0/INT0)
unnamed: LED2.A, R1.2
unnamed: U3.16 (USBDM), X1.D-
unnamed: LED3.A, R3.2
unnamed: U3.15 (USBDP), X1.D+
unnamed: LED1.A, R5.2
unnamed: R4.1, U1.5 (HR)
unnamed: R2.1, U1.7 (RESET)
unnamed: C1.2, Q1.P$1 (2), U1.4 (OSC)
unnamed: C2.2, Q1.P$2 (1), U1.3 (F32KIN)
OP0: R7.1, SJ2.2, U2.6 (RA4)
OP1: SJ3.2, U2.22 (RB1)
OP2: SJ4.2, U2.23 (RB2)
OP3: SJ5.2, U2.24 (RB3)
OP4: SJ6.2, U2.25 (RB4)
OP5: SJ7.2, U2.26 (RB5)
P0: JP3.5, U2.11 (RC0)
P1: JP3.6, U2.12 (RC1)
P2: U2.13 (RC2)
P3: U2.14 (RC3)
P4: U2.15 (RC4/SD0)
PGC: SJ8.2, U2.27 (RB6/PGC), U10.2 (PGC)
PGD: SJ9.2, U2.28 (RB7/PGD), U10.3 (PGD)
RST: R2.2, U2.7 (RA5/AN4)
RX: JP2.4, U2.17 (TX/RC6/SCL), U3.5 (RXD)
RXLED: LED3.C, U3.22 (RXLED)
STAT: LED1.C, U2.16 (RC5)
TX: JP2.3, SJ1.2, U2.18 (RX/RC7/SDA)
TXLED: LED2.C, U3.23 (TXLED)
USB-TX: SJ1.1, U3.1 (TXD)
VBUS: F1.1, X1.VBUS
VPP: R6.1, U2.1 (MCLR/VPP), U10.6 (VPP)

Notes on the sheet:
v17

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
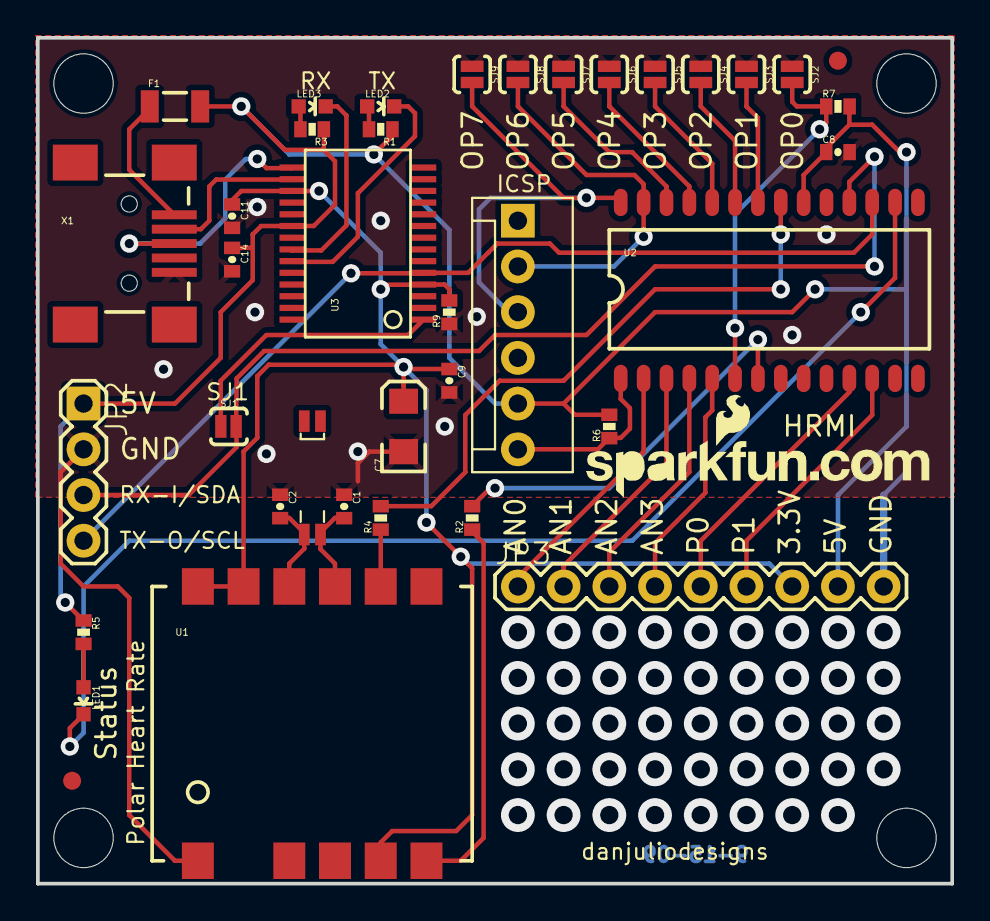
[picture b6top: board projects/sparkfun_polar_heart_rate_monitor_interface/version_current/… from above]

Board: 2 copper layers, 50.8 x 47.0 mm, 43 parts (0 on the bottom side), 36 nets.

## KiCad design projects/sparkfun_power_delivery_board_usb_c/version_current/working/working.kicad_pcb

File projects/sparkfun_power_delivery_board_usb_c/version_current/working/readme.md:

# OOMP Project  
## Power_Delivery_Board-USB-C  by sparkfun  
  
oomp key: oomp_projects_flat_sparkfun_power_delivery_board_usb_c  
(snippet of original readme)  
  
SparkFun Power Delivery Board - USB-C  
========================================  

[*SparkFun Power Delivery Board - USB-C (15801)*](https://www.sparkfun.com/products/15801)  
  
<Basic description of the part.>  
  
Repository Contents  
-------------------  
  
* **/Hardware** - Eagle design files (.brd, .sch)  
  
Documentation  
--------------  
* **[Hookup Guide](https://learn.sparkfun.com/tutorials/power-delivery-board---usb-c-qwiic-hookup-guide)** - Basic hookup guide for the Power Delivery Board - USB-C.  
* **[Arduino Library](https://github.com/sparkfun/SparkFun_STUSB4500_Arduino_Library)** - Arduino Library for use with the Power Delivery Board.  
* **[SparkFun Fritzing repo](https://github.com/sparkfun/Fritzing_Parts)** - Fritzing diagrams for SparkFun products.  
  
License Information  
-------------------  
  
This product is _**open source**_!   
  
Please review the LICENSE.md file for license information.   
  
If you have any questions or concerns on licensing, please contact technical support on our [SparkFun forums](https://forum.sparkfun.com/viewforum.php?f=152).  
  
Distributed as-is; no warranty is given.  
  
- Your friends at SparkFun.  
  
_<COLLABORATION CREDIT>_  
  
  full source readme at [readme_src.md](readme_src.md)  
  
source repo at: [https://github.com/sparkfun/Power_Delivery_Board-USB-C](https://github.com/sparkfun/Power_Delivery_Board-USB-C)  
## Board  

## Schematic  

[schematic pdf](working_schematic.pdf)  
## Images

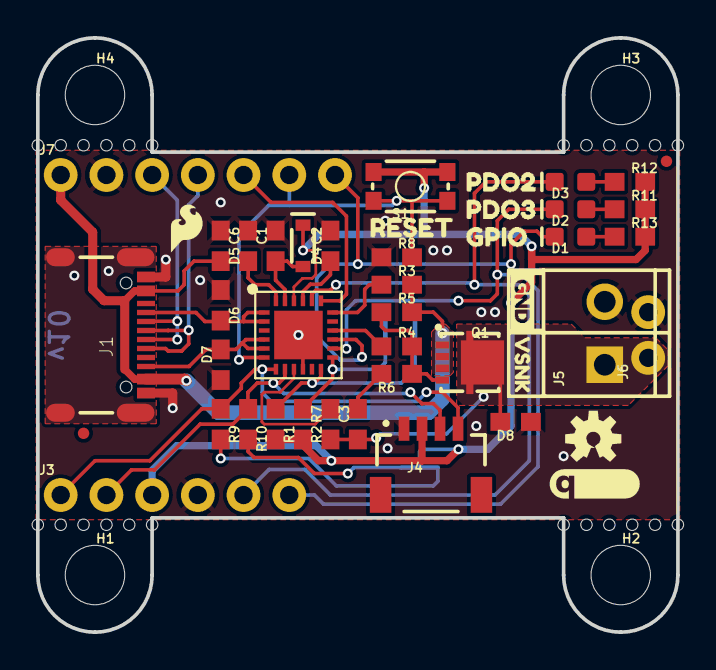
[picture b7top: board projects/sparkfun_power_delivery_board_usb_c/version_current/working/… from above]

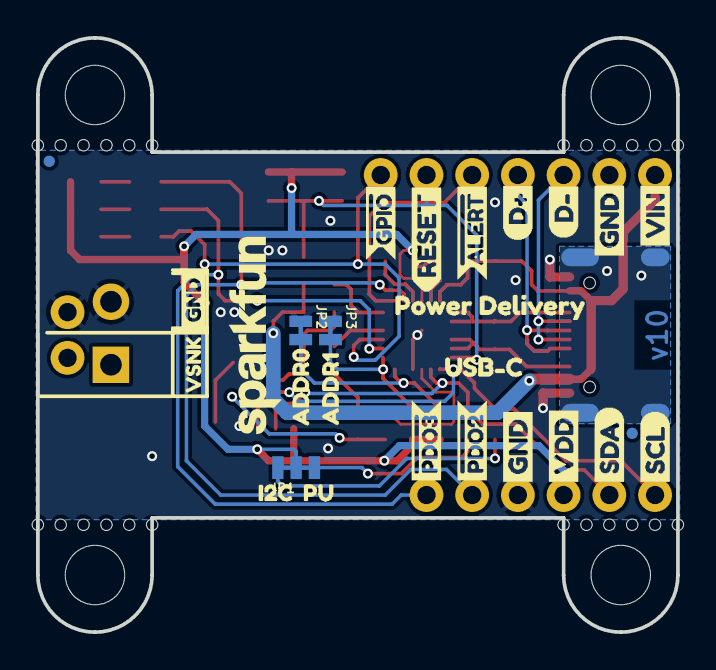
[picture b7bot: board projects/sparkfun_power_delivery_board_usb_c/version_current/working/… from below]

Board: 2 copper layers, 35.6 x 33.0 mm, 101 parts (27 on the bottom side), 30 nets.

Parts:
@HOLE0, @HOLE1, @HOLE2, @HOLE3, @HOLE4, @HOLE5, @HOLE6, @HOLE7, @HOLE8, @HOLE9, @HOLE10, @HOLE11, @HOLE12, @HOLE13, @HOLE14, @HOLE15, @HOLE16, @HOLE17, @HOLE18, @HOLE19, @HOLE20, @HOLE21, @HOLE22, @HOLE23: (no value)
C1, C2, C6: 1.0uF; 0603
C3: 0.1uF; 0603
D1: BLUE; LED-0603
D2: Yellow; LED-0603
D3: GREEN; LED-0603
D4: BAT60A; SOD-323
D5, D6, D7, D8: 24V; 0603
FD1, FD2, FD3, FD4: FIDUCIALUFIDUCIAL; FIDUCIAL-MICRO
FRAME1: FRAME-LETTER; CREATIVE_COMMONS
H1, H2, H3, H4: STAND-OFF
J1: USB-C-16P
J3: 1X06_NO_SILK
J4: QWIIC; JST04_1MM_RA
J5: SCREWTERMINAL-3.5MM-2
J6: 1X02_NO_SILK
J7: 1X07_NO_SILK
JP1: SMT-JUMPER_3_2-NC_TRACE_NO-SILK
JP2, JP3: SMT-JUMPER_2_NC_TRACE_NO-SILK
LOGO1: OSHW-LOGOS; OSHW-LOGO-S
LOGO2: SFE_LOGO_NAME.1_INCH; SFE_LOGO_NAME_.1
LOGO3: QWIIC_LOGO_5MM; QWIIC_5MM
Q1: 9A/30V/15mΩ; 8-POWERVDFN-3X3
R1, R2, R5, R8: 100k; 0603
R3, R7, R11, R12, R13: 1k; 0603
R4: 22k; 0603
R6: 100; 0603
R9, R10: 2.2k; 0603
S1: TACTILE_SWITCH_SMD_4.6X2.8MM
U1: STUSB4500; QFN-24
U$1: VDD2
U$2, U$11: GND6
U$3: SDA11
U$4: SCL12
U$5: #GPIO0
U$7: D#8
U$8: D#7
U$9: USB#C1
U$10: RESET10
U$12: VIN6
U$13: I2C2
U$14: PU3
U$15: ADDR00
U$16: ADDR11
U$17: RESET7
U$18: GPIO1
U$19: PDO24
U$20: PDO35
U$21, U$24: VSNK1
U$22, U$23: GND0
U$25: SFE_LOGO_FLAME_.1
U$26: #ALERT0
U$27: _POWER_DELIVERY2
U$29: #PDO20
U$30: #PDO31

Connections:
1.2V: C2.1, U1.P$21
2.7V: C1.1, D4.A, U1.P$23
ADDR0: JP2.2, R1.1, U1.P$12
ADDR1: JP3.2, R2.1, U1.P$13
CC1: D6.2, J1.A5, U1.P$1, U1.P$2
CC2: D7.2, J1.B5, U1.P$4, U1.P$5
D+: J1.A6, J1.B6, J7.4
D-: J1.A7, J1.B7, J7.3
DISCH: R7.2, U1.P$9
EN_SNK: R4.1, U1.P$16
GND: C1.2, C2.2, C6.2, D5.1, D6.1, D7.1, D8.1, J1.GND, J1.GND2, J3.4, J4.1, J5.2, J6.2, J7.2, JP2.1, JP3.1, R8.1, U1.P$10, U1.P$25
GPIO: D1.C, J7.7, U1.P$15
unnamed: D2.A, R11.1
unnamed: D3.A, R12.1
unnamed: JP1.3, R9.2
unnamed: JP1.1, R10.2
unnamed: Q1.4, R4.2, R5.1, R6.1
unnamed: C3.2, R6.2
unnamed: D1.A, R13.1
POWER_PDO2: D3.C, J3.5, U1.P$20
POWER_PDO3: D2.C, J3.6, U1.P$14
RESET: J7.6, R8.2, S1.3, S1.4, U1.P$6
SCL: J3.1, J4.4, R9.1, U1.P$7
SDA: J3.2, J4.3, R10.1, U1.P$8
SHIELD: J1.SHLD1, J1.SHLD2, J1.SHLD3, J1.SHLD4, J1.SHLD5, J1.SHLD6, J1.SHLD7, J1.SHLD8
VBUS_VS_DISCH: R3.1, U1.P$18
VDD: D4.C, J3.3, J4.2, JP1.2, R1.2, R2.2, R11.2, R12.2, R13.2, S1.1, S1.2, U1.P$22
VIN: C6.1, D5.2, J1.VBUS1, J1.VBUS2, J7.1, Q1.1, Q1.2, Q1.3, R3.2, R5.2, U1.P$24
VSNK: C3.1, D8.2, J5.1, J6.1, Q1.5@1, Q1.5@2, Q1.5@3, R7.1
~ALERT: J7.5, U1.P$19
